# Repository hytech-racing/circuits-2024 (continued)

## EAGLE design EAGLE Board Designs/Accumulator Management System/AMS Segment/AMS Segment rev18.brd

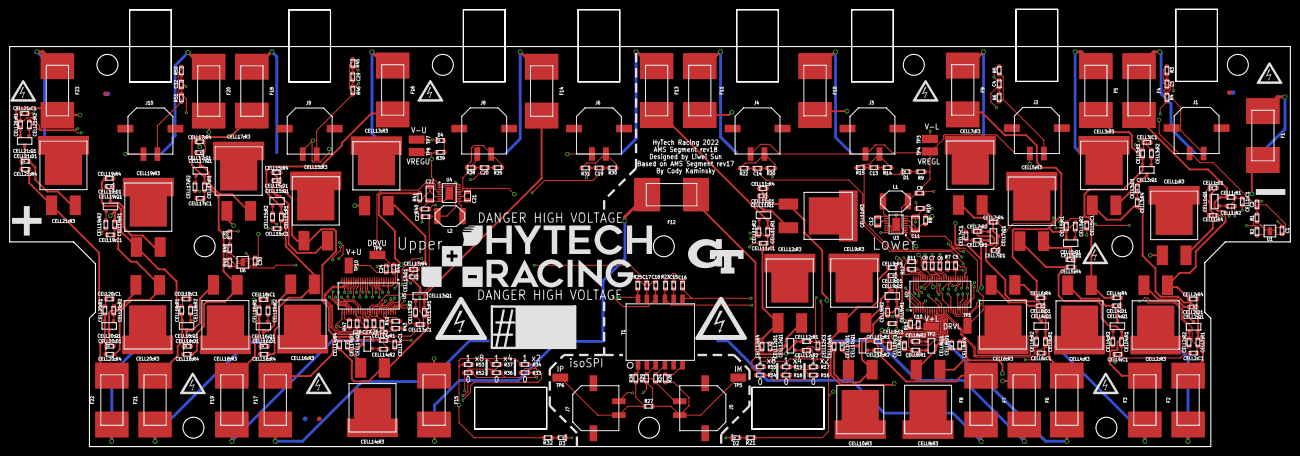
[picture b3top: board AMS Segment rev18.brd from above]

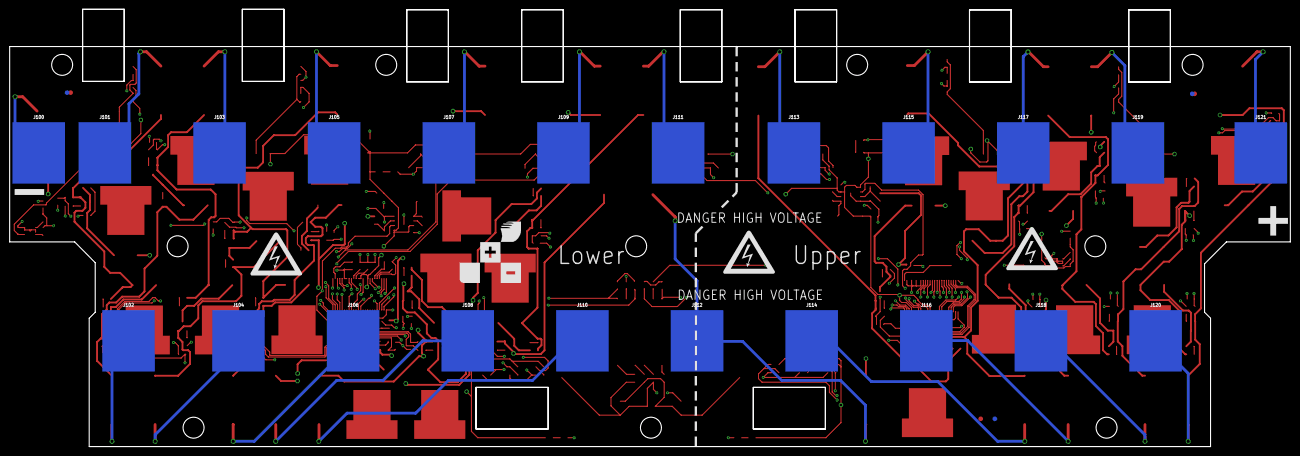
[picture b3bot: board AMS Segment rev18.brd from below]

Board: 4 copper layers, 275.2 x 94.0 mm, 347 parts (29 on the bottom side), 220 nets.

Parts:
C1, C30: CAPACITOR_0603_10V_0.1UF; 0603-CAP
C2, C31: CAPACITOR_0603_10V_3.3NF; 0603-CAP
C3, C4, C5, C13, C14, C19, C20, C28, C29, C32: CAPACITOR_0603_100V_10NF; 0603-CAP
C6, C7, C8, C23, C26, C27: CAPACITOR_0603_10V_1UF; 0603-CAP
C9, C25: CAPACITOR_0603_10V_22UF; 0603-CAP
C10, C24: CAPACITOR_0603_100V_0.1UF; 0603-CAP
C11, C22: CAPACITOR_1206_100V_2.2UF; 1206-CAP
C12, C21: CAPACITOR_0805_100V_0.22UF; 0805-CAP
C15, C17: CAPACITOR_0603_10V_10NF; 0603-CAP
C16, C18: CAPACITOR_0603_10V_15PF; 0603-CAP
CELL1:C1, CELL2:C1, CELL3:C1, CELL4:C1, CELL5:C1, CELL6:C1, CELL7:C1, CELL8:C1, CELL9:C1, CELL10:C1, CELL11:C1, CELL12:C1, CELL13:C1, CELL14:C1, CELL15:C1, CELL16:C1, CELL17:C1, CELL18:C1, CELL19:C1, CELL20:C1, CELL21:C1: CAPACITOR_0603_100V_10NF; 0603-CAP
CELL1:D1, CELL2:D1, CELL3:D1, CELL4:D1, CELL5:D1, CELL6:D1, CELL7:D1, CELL8:D1, CELL9:D1, CELL10:D1, CELL11:D1, CELL12:D1, CELL13:D1, CELL14:D1, CELL15:D1, CELL16:D1, CELL17:D1, CELL18:D1, CELL19:D1, CELL20:D1, CELL21:D1: LED_0603_RED; 0603-LED
CELL1:Q1, CELL2:Q1, CELL3:Q1, CELL4:Q1, CELL5:Q1, CELL6:Q1, CELL7:Q1, CELL8:Q1, CELL9:Q1, CELL10:Q1, CELL11:Q1, CELL12:Q1, CELL13:Q1, CELL14:Q1, CELL15:Q1, CELL16:Q1, CELL17:Q1, CELL18:Q1, CELL19:Q1, CELL20:Q1, CELL21:Q1: TRANSISTOR_P_MOS_SOT23_SI2369DS-T1-GE3; SOT-23
CELL1:R1, CELL2:R1, CELL3:R1, CELL4:R1, CELL5:R1, CELL6:R1, CELL7:R1, CELL8:R1, CELL9:R1, CELL10:R1, CELL11:R1, CELL12:R1, CELL13:R1, CELL14:R1, CELL15:R1, CELL16:R1, CELL17:R1, CELL18:R1, CELL19:R1, CELL20:R1, CELL21:R1: RESISTOR_0603_100; 0603-RES
CELL1:R2, CELL1:R4, CELL2:R2, CELL2:R4, CELL3:R2, CELL3:R4, CELL4:R2, CELL4:R4, CELL5:R2, CELL5:R4, CELL6:R2, CELL6:R4, CELL7:R2, CELL7:R4, CELL8:R2, CELL8:R4, CELL9:R2, CELL9:R4, CELL10:R2, CELL10:R4, CELL11:R2, CELL11:R4, CELL12:R2, CELL12:R4, CELL13:R2, CELL13:R4, CELL14:R2, CELL14:R4, CELL15:R2, CELL15:R4, CELL16:R2, CELL16:R4, CELL17:R2, CELL17:R4, CELL18:R2, CELL18:R4, CELL19:R2, CELL19:R4, CELL20:R2, CELL20:R4, CELL21:R2, CELL21:R4: RESISTOR_0603_1K; 0603-RES
CELL1:R3, CELL2:R3, CELL3:R3, CELL4:R3, CELL5:R3, CELL6:R3, CELL7:R3, CELL8:R3, CELL9:R3, CELL10:R3, CELL11:R3, CELL12:R3, CELL13:R3, CELL14:R3, CELL15:R3, CELL16:R3, CELL17:R3, CELL18:R3, CELL19:R3, CELL20:R3, CELL21:R3: RESISTOR_PWR263_7.5; PWR263
D1, D2, D3, D4: LED_0603_BLUE; 0603-LED
F1, F2, F3, F4, F5, F6, F7, F8, F9, F10, F11, F12, F13, F14, F15, F16, F17, F18, F19, F20, F21, F22, F23: FUSE_0885_1; 0885
J1, J2, J3, J4, J5, J6, J7, J8, J9, J10: CONNECTOR-2_MICROFIT_SMD_RIGHTANGLE_02_SINGLE_BLA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; MOLEX_MICROFIT_SMD_RIGHTANGLE_02_SINGLE
J100, J101, J102, J103, J104, J105, J106, J107, J108, J109, J110, J111, J112, J113, J114, J115, J116, J117, J118, J119, J120, J121: CONNECTOR-1_5222_; 5222
L1, L2: INDUCTOR_74451133_33UH; 74451133
R1, R4, R6, R7, R13, R15, R22, R31, R35, R44, R46, R47, R49, R51: RESISTOR_0603_100; 0603-RES
R2, R16, R17, R18, R19, R27, R33, R34, R36, R37, R48, R52, R53, R54, R55: RESISTOR_0603_DNP; 0603-RES
R3, R5, R14, R20, R30, R38, R45, R50: RESISTOR_0603_2.74K; 0603-RES
R8, R41: RESISTOR_0603_470; 0603-RES
R9, R11, R12, R21, R32, R39, R42, R43: RESISTOR_0603_1K; 0603-RES
R10, R40: RESISTOR_0603_374K; 0603-RES
R23, R25: RESISTOR_0603_402; 0603-RES
R24, R26, R28, R29: RESISTOR_0603_22; 0603-RES
T1: TRANSFORMER_HM2112ZNLT; HM2112ZNLT
TP1, TP2, TP3, TP4, TP5, TP6, TP7, TP8, TP9, TP10: TEST_POINT; MICRO_MINIATURE
U1, U6: SHT31-ARP-B; DFN-8
U2, U5: LTC6811-2; SSOP-48
U3, U4: LT3990-5; MSOP-16(MSE)
U$1, U$5, U$6, U$7, U$18, U$20, U$23, U$25: HV_0.50"
U$2, U$3, U$4, U$8, U$11, U$12, U$17, U$21, U$22, U$24: MOUNTING_M4
U$9, U$16: HV_1.00"
U$10: LOGO_GT_MEDIUM
U$13, U$14: DANGER_HIGH_VOLTAGE
U$15: NUMBER
U$19: LOGO_HYTECH_LARGE
U$26: LOGO_HYTECH_SQUARE_EXTRA_LARGE
U$27, U$28, U$29, U$31, U$32, U$33: FIDUCIAL_1MM
U$101, U$102, U$103: HV_LARGE

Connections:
C0L: C5.1, R7.2, U2.26
C0U: C28.1, R47.2, U5.26
C1L: CELL1:C1.1, CELL1:R1.2, U2.24
C1U: CELL13:C1.1, CELL13:R1.2, U5.24
C2L: CELL2:C1.1, CELL2:R1.2, U2.22
C2U: CELL14:C1.1, CELL14:R1.2, U5.22
C3L: CELL3:C1.1, CELL3:R1.2, U2.20
C3U: CELL15:C1.1, CELL15:R1.2, U5.20
C4L: CELL4:C1.1, CELL4:R1.2, U2.18
C4U: CELL16:C1.1, CELL16:R1.2, U5.18
C5L: CELL5:C1.1, CELL5:R1.2, U2.16
C5U: CELL17:C1.1, CELL17:R1.2, U5.16
C6L: CELL6:C1.1, CELL6:R1.2, U2.14
C6U: CELL18:C1.1, CELL18:R1.2, U5.14
C7L: CELL7:C1.1, CELL7:R1.2, U2.12
C7U: CELL19:C1.1, CELL19:R1.2, U5.12
C8L: CELL8:C1.1, CELL8:R1.2, U2.10
C8U: CELL20:C1.1, CELL20:R1.2, U5.10
C9L: CELL9:C1.1, CELL9:R1.2, U2.8
C9U: CELL21:C1.1, CELL21:R1.2, U5.2, U5.4, U5.6, U5.8
C10L: CELL10:C1.1, CELL10:R1.2, U2.6
C11L: CELL11:C1.1, CELL11:R1.2, U2.4
C12L: CELL12:C1.1, CELL12:R1.2, U2.2
CC0: F1.1, J100.1
CC1: F4.1, J101.1
CC2: F2.1, J102.1
CC3: F5.1, J103.1
CC4: F3.1, J104.1
CC5: F9.1, J105.1
CC6: F6.1, J106.1
CC7: F10.1, J107.1
CC8: F7.1, J108.1
CC9: F11.1, J109.1
CC10: F8.1, J110.1
CC11: F13.1, J111.1
CC12: F12.1, F15.1, J112.1
CC13: F14.1, J113.1
CC14: F17.1, J114.1
CC15: F16.1, J115.1
CC16: F19.1, J116.1
CC17: F18.1, J117.1
CC18: F21.1, J118.1
CC19: F20.1, J119.1
CC20: F22.1, J120.1
CC21: F23.1, J121.1
CELL1:LED: CELL1:D1.1, CELL1:R4.2
CELL1:QD: CELL1:D1.2, CELL1:Q1.3, CELL1:R3.2
CELL1:QG: CELL1:Q1.1, CELL1:R2.1
CELL2:LED: CELL2:D1.1, CELL2:R4.2
CELL2:QD: CELL2:D1.2, CELL2:Q1.3, CELL2:R3.2
CELL2:QG: CELL2:Q1.1, CELL2:R2.1
CELL3:LED: CELL3:D1.1, CELL3:R4.2
CELL3:QD: CELL3:D1.2, CELL3:Q1.3, CELL3:R3.2
CELL3:QG: CELL3:Q1.1, CELL3:R2.1
CELL4:LED: CELL4:D1.1, CELL4:R4.2
CELL4:QD: CELL4:D1.2, CELL4:Q1.3, CELL4:R3.2
CELL4:QG: CELL4:Q1.1, CELL4:R2.1
CELL5:LED: CELL5:D1.1, CELL5:R4.2
CELL5:QD: CELL5:D1.2, CELL5:Q1.3, CELL5:R3.2
CELL5:QG: CELL5:Q1.1, CELL5:R2.1
CELL6:LED: CELL6:D1.1, CELL6:R4.2
CELL6:QD: CELL6:D1.2, CELL6:Q1.3, CELL6:R3.2
CELL6:QG: CELL6:Q1.1, CELL6:R2.1
CELL7:LED: CELL7:D1.1, CELL7:R4.2
CELL7:QD: CELL7:D1.2, CELL7:Q1.3, CELL7:R3.2
CELL7:QG: CELL7:Q1.1, CELL7:R2.1
CELL8:LED: CELL8:D1.1, CELL8:R4.2
CELL8:QD: CELL8:D1.2, CELL8:Q1.3, CELL8:R3.2
CELL8:QG: CELL8:Q1.1, CELL8:R2.1
CELL9:LED: CELL9:D1.1, CELL9:R4.2
CELL9:QD: CELL9:D1.2, CELL9:Q1.3, CELL9:R3.2
CELL9:QG: CELL9:Q1.1, CELL9:R2.1
CELL10:LED: CELL10:D1.1, CELL10:R4.2
CELL10:QD: CELL10:D1.2, CELL10:Q1.3, CELL10:R3.2
CELL10:QG: CELL10:Q1.1, CELL10:R2.1
CELL11:LED: CELL11:D1.1, CELL11:R4.2
CELL11:QD: CELL11:D1.2, CELL11:Q1.3, CELL11:R3.2
CELL11:QG: CELL11:Q1.1, CELL11:R2.1
CELL12:LED: CELL12:D1.1, CELL12:R4.2
CELL12:QD: CELL12:D1.2, CELL12:Q1.3, CELL12:R3.2
CELL12:QG: CELL12:Q1.1, CELL12:R2.1
CELL13:LED: CELL13:D1.1, CELL13:R4.2
CELL13:QD: CELL13:D1.2, CELL13:Q1.3, CELL13:R3.2
CELL13:QG: CELL13:Q1.1, CELL13:R2.1
CELL14:LED: CELL14:D1.1, CELL14:R4.2
CELL14:QD: CELL14:D1.2, CELL14:Q1.3, CELL14:R3.2
CELL14:QG: CELL14:Q1.1, CELL14:R2.1
CELL15:LED: CELL15:D1.1, CELL15:R4.2
CELL15:QD: CELL15:D1.2, CELL15:Q1.3, CELL15:R3.2
CELL15:QG: CELL15:Q1.1, CELL15:R2.1
CELL16:LED: CELL16:D1.1, CELL16:R4.2
CELL16:QD: CELL16:D1.2, CELL16:Q1.3, CELL16:R3.2
CELL16:QG: CELL16:Q1.1, CELL16:R2.1
CELL17:LED: CELL17:D1.1, CELL17:R4.2
CELL17:QD: CELL17:D1.2, CELL17:Q1.3, CELL17:R3.2
CELL17:QG: CELL17:Q1.1, CELL17:R2.1
CELL18:LED: CELL18:D1.1, CELL18:R4.2
CELL18:QD: CELL18:D1.2, CELL18:Q1.3, CELL18:R3.2
CELL18:QG: CELL18:Q1.1, CELL18:R2.1
CELL19:LED: CELL19:D1.1, CELL19:R4.2
CELL19:QD: CELL19:D1.2, CELL19:Q1.3, CELL19:R3.2
CELL19:QG: CELL19:Q1.1, CELL19:R2.1
CELL20:LED: CELL20:D1.1, CELL20:R4.2
CELL20:QD: CELL20:D1.2, CELL20:Q1.3, CELL20:R3.2
CELL20:QG: CELL20:Q1.1, CELL20:R2.1
CELL21:LED: CELL21:D1.1, CELL21:R4.2
CELL21:QD: CELL21:D1.2, CELL21:Q1.3, CELL21:R3.2
CELL21:QG: CELL21:Q1.1, CELL21:R2.1
DRVL: TP1.1, U2.38, U3.4
DRVU: TP9.1, U4.4, U5.38
GPIO1L: C14.1, R22.2, U2.27
GPIO1U: C32.2, R51.1, U5.27
GPIO2L: C13.1, R15.2, U2.28
GPIO2U: C29.1, R46.2, U5.28
GPIO3L: C4.1, R6.2, U2.29
GPIO3U: C20.1, R35.2, U5.29
GPIO4L: C3.2, R4.2, U2.32
GPIO4U: C19.1, R31.2, U5.32
GPIO5L: C2.1, R1.1, R2.1, U2.33
GPIO5U: C31.1, R48.1, R49.2, U5.33
IM: J5.2, J7.2, R26.1, R27.1, R29.1, TP5.1
IML: C16.2, T1.7, U2.41
IMU: C18.2, T1.10, U5.41
IP: J5.1, J7.1, R24.1, R27.2, R28.1, TP6.1
IPL: R23.2, T1.9, U2.42
IPU: R25.2, T1.12, U5.42
unnamed: R40.2, U4.16
unnamed: D1.2, R9.1
unnamed: C21.2, L2.1, U4.9
unnamed: C21.1, U4.11
unnamed: D3.2, R32.1
unnamed: D2.2, R21.1
unnamed: R10.2, U3.16
unnamed: R54.1, R55.2, U2.48
unnamed: D4.2, R39.1
unnamed: C12.2, L1.1, U3.9
unnamed: C12.1, U3.11
unnamed: R48.2, U6.1
unnamed: R52.1, R53.2, U5.48
unnamed: C17.2, T1.11
unnamed: R29.2, T1.3
unnamed: R33.1, R34.2, U5.46
unnamed: R28.2, T1.1
unnamed: C15.2, T1.8
unnamed: R49.1, U6.4
unnamed: R26.2, T1.6
unnamed: R24.2, T1.4
unnamed: R36.1, R37.2, U5.47
unnamed: R42.2, R43.2, U5.43
unnamed: R16.1, R17.2, U2.46
unnamed: R18.1, R19.2, U2.47
unnamed: R42.1, U5.44
unnamed: J10.2, R50.1, R51.2
unnamed: R11.2, R12.1, U2.43
unnamed: R12.2, U2.44
unnamed: J9.2, R45.1, R46.1
unnamed: J8.2, R35.1, R38.1
unnamed: J6.2, R30.1, R31.1
unnamed: R1.2, U1.1
unnamed: R2.2, U1.4
unnamed: J4.2, R20.1, R22.1
unnamed: J3.2, R14.1, R15.1
unnamed: J2.2, R5.1, R6.1
unnamed: J1.2, R3.2, R4.1
unnamed: C18.1, R25.1
unnamed: C16.1, R23.1
S1L: CELL1:R2.2, U2.25
S1U: CELL13:R2.2, U5.25
S2L: CELL2:R2.2, U2.23
S2U: CELL14:R2.2, U5.23
S3L: CELL3:R2.2, U2.21
S3U: CELL15:R2.2, U5.21
S4L: CELL4:R2.2, U2.19
S4U: CELL16:R2.2, U5.19
S5L: CELL5:R2.2, U2.17
S5U: CELL17:R2.2, U5.17
S6L: CELL6:R2.2, U2.15
S6U: CELL18:R2.2, U5.15
S7L: CELL7:R2.2, U2.13
S7U: CELL19:R2.2, U5.13
S8L: CELL8:R2.2, U2.11
S8U: CELL20:R2.2, U5.11
S9L: CELL9:R2.2, U2.9
S9U: CELL21:R2.2, U5.9
S10L: CELL10:R2.2, U2.7
S11L: CELL11:R2.2, U2.5
S12L: CELL12:R2.2, U2.3
SENSE1: CELL1:Q1.2, CELL1:R1.1, CELL2:R3.1, CELL2:R4.1, F4.2
SENSE2: CELL2:Q1.2, CELL2:R1.1, CELL3:R3.1, CELL3:R4.1, F2.2
SENSE3: CELL3:Q1.2, CELL3:R1.1, CELL4:R3.1, CELL4:R4.1, F5.2
SENSE4: CELL4:Q1.2, CELL4:R1.1, CELL5:R3.1, CELL5:R4.1, F3.2
SENSE5: CELL5:Q1.2, CELL5:R1.1, CELL6:R3.1, CELL6:R4.1, F9.2
SENSE6: CELL6:Q1.2, CELL6:R1.1, CELL7:R3.1, CELL7:R4.1, F6.2
SENSE7: CELL7:Q1.2, CELL7:R1.1, CELL8:R3.1, CELL8:R4.1, F10.2
SENSE8: CELL8:Q1.2, CELL8:R1.1, CELL9:R3.1, CELL9:R4.1, F7.2
SENSE9: CELL9:Q1.2, CELL9:R1.1, CELL10:R3.1, CELL10:R4.1, F11.2
SENSE10: CELL10:Q1.2, CELL10:R1.1, CELL11:R3.1, CELL11:R4.1, F8.2
SENSE11: CELL11:Q1.2, CELL11:R1.1, CELL12:R3.1, CELL12:R4.1, F13.2
SENSE12: CELL12:Q1.2, CELL12:R1.1, F12.2, R8.1, R13.2
SENSE13: CELL13:Q1.2, CELL13:R1.1, CELL14:R3.1, CELL14:R4.1, F14.2
SENSE14: CELL14:Q1.2, CELL14:R1.1, CELL15:R3.1, CELL15:R4.1, F17.2
SENSE15: CELL15:Q1.2, CELL15:R1.1, CELL16:R3.1, CELL16:R4.1, F16.2
SENSE16: CELL16:Q1.2, CELL16:R1.1, CELL17:R3.1, CELL17:R4.1, F19.2
SENSE17: CELL17:Q1.2, CELL17:R1.1, CELL18:R3.1, CELL18:R4.1, F18.2
SENSE18: CELL18:Q1.2, CELL18:R1.1, CELL19:R3.1, CELL19:R4.1, F21.2
SENSE19: CELL19:Q1.2, CELL19:R1.1, CELL20:R3.1, CELL20:R4.1, F20.2
SENSE20: CELL20:Q1.2, CELL20:R1.1, CELL21:R3.1, CELL21:R4.1, F22.2
SENSE21: CELL21:Q1.2, CELL21:R1.1, F23.2, R41.1, R44.1
V+L: C10.1, R13.1, TP2.1, U2.1
V+U: C24.1, R44.2, TP10.1, U5.1
V-L: C1.1, C2.2, C3.1, C4.2, C5.2, C6.2, C7.2, C8.2, C9.2, C10.2, C11.2, C13.2, C14.2, C15.1, CELL1:C1.2, CELL1:R3.1, CELL1:R4.1, CELL2:C1.2, CELL3:C1.2, CELL4:C1.2, CELL5:C1.2, CELL6:C1.2, CELL7:C1.2, CELL8:C1.2, CELL9:C1.2, CELL10:C1.2, CELL11:C1.2, CELL12:C1.2, D1.1, D2.1, F1.2, R3.1, R5.2, R7.1, R10.1, R11.1, R14.2, R16.2, R18.2, R20.2, R54.2, TP3.1, U1.2, U1.3, U1.7, U1.8, U1.PAD, U2.30, U2.31, U2.45, U3.8, U3.17
V-U: C17.1, C19.2, C20.2, C22.2, C23.2, C24.2, C25.2, C26.2, C27.2, C28.2, C29.2, C30.2, C31.2, C32.1, CELL13:C1.2, CELL13:R3.1, CELL13:R4.1, CELL14:C1.2, CELL15:C1.2, CELL16:C1.2, CELL17:C1.2, CELL18:C1.2, CELL19:C1.2, CELL20:C1.2, CELL21:C1.2, D3.1, D4.1, F15.2, R30.2, R33.2, R36.2, R38.2, R40.1, R43.1, R45.2, R47.1, R50.2, R52.2, TP7.1, U4.8, U4.17, U5.30, U5.31, U6.2, U6.3, U6.7, U6.8, U6.PAD
VINL: C11.1, R8.2, U3.6
VINU: C22.1, R41.2, U4.6
VREF1L: C7.1, U2.35
VREF1U: C26.1, U5.35
VREF2L: C6.1, U2.34
VREF2U: C27.1, U5.34
VREGL: C1.2, C8.1, C9.1, J1.1, J2.1, J3.1, J4.1, L1.2, R9.2, R17.1, R19.1, R21.2, R55.1, TP4.1, U1.5, U2.36, U2.37, U2.40, U3.1, U3.2, U3.13
VREGU: C23.1, C25.1, C30.1, J6.1, J8.1, J9.1, J10.1, L2.2, R32.2, R34.1, R37.1, R39.2, R53.1, TP8.1, U4.1, U4.2, U4.13, U5.36, U5.37, U5.40, U5.45, U6.5

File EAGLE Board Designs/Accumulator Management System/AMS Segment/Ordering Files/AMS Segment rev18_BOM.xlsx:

Board Quantity | Value | Reference Designator | CAPACITANCE | COLOR | CURRENT | CURRENT_RATED | CURRENT_SATURATION | DCR | DKPN | GAUGE | INDUCTANCE | MANUFACTURER | MODEL | Mouser Part Number | MPN | Alternative MPN | POWER | RESISTANCE | TOLERANCE | TOLERANCE_B | TOLERANCE_RESISTANCE | VOLTAGE | VOLTAGE_CONTINUOUS | VOLTAGE_MAX
2 | CAPACITOR_0603_100V_0.1UF | C10, C24 | 0.1µF |  |  |  |  |  | 311-1523-1-ND |  |  | Yageo |  | 603-CC603KRX7R0BB104 | CC0603KRX7R0BB104 |  |  |  | 0.1 |  |  | 100V
31 | CAPACITOR_0603_100V_10NF | C3, C4, C5, C13, C14, C19, C20, C28, C29, C32, CELL1:C1, CELL2:C1, CELL3:C1, CE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 | 10nF |  |  |  |  |  | 311-1788-1-ND |  |  | Yageo |  | 603-CC603KRX7R0BB103 | CC0603KRX7R0BB103 |  |  |  | 0.1 |  |  | 100V
2 | CAPACITOR_0603_10V_0.1UF | C1, C30 | 0.1µF |  |  |  |  |  | 720-1688-1-ND |  |  | Vishay Vitramon |  | 77-VJ0603Y104JXQPBC | VJ0603Y104JXQPW1BC |  |  |  | 0.05 |  |  | 10V
2 | CAPACITOR_0603_10V_10NF | C15, C17 | 10nF |  |  |  |  |  | 311-4054-1-ND |  |  | Yageo |  | 603-CC603KRX7R6BB103 | CC0603KRX7R6BB103 |  |  |  | 0.1 |  |  | 10V
2 | CAPACITOR_0603_10V_15PF | C16, C18 | 15pF |  |  |  |  |  | 720-VJ0603A150FXQPW1BCCT-ND |  |  | Vishay Vitramon |  | 77-VJ0603A150FXQPBC | VJ0603A150FXQPW1BC |  |  |  | 0.01 |  |  | 10V
6 | CAPACITOR_0603_10V_1UF | C6, C7, C8, C23, C26, C27 | 1µF |  |  |  |  |  | 311-1796-1-ND |  |  | Yageo |  | 603-CC603KRX7R6BB105 | CC0603KRX7R6BB105 |  |  |  | 0.1 |  |  | 10V
2 | CAPACITOR_0603_10V_22UF | C9, C25 | 22µF |  |  |  |  |  | 490-10476-1-ND |  |  | Murata Electronics |  | 81-GRM188R61A226ME5D | GRM188R61A226ME15D |  |  |  | 0.2 |  |  | 10V
2 | CAPACITOR_0603_10V_3.3NF | C2, C31 | 3.3nF |  |  |  |  |  | 732-7759-1-ND |  |  | WÃ¼rth Elektronik |  | 710-885012006016 | 885012006016 |  |  |  | 0.05 |  |  | 10V
2 | CAPACITOR_0805_100V_0.22UF | C12, C21 | 0.22µF |  |  |  |  |  | 399-8049-1-ND |  |  | KEMET |  | 80-C0805C224K1R | C0805C224K1RACTU |  |  |  | 0.1 |  |  | 100V
2 | CAPACITOR_1206_100V_2.2UF | C11, C22 | 2.2µF |  |  |  |  |  | 478-12144-1-ND |  |  | AVX Corporation |  | 581-12061C225K4T2A | 12061C225K4T2A |  |  |  | 0.1 |  |  | 100V
22 | CONNECTOR-1_5222_ | J100, J101, J102, J103, J104, J105, J106, J107, J108, J109, J110, J111, J112, J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 |  |  |  |  |  |  | 36-5222-ND |  |  | Keystone Electronics | SPRING | 534-5222 | 5222
10 | CONNECTOR-2_MICROFIT_SMD_RIGHTANGLE_02_SINGLE_BLACK | J1, J2, J3, J4, J5, J6, J7, J8, J9, J10 |  |  |  |  |  |  | WM14310CT-ND |  |  | Molex |  | 538-43650-0214 | 436500214
20 | CRIMP_MICROFIT_20-24 | O17, O18, O19, O20, O21, O22, O23, O24, O25, O26, O27, O28, O29, O30, O31, O32,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 |  |  |  |  |  |  | WM2776CT-ND | 20-24 |  | Molex |  | 538-43030-0003 | 430300003
23 | FUSE_0885_1 | F1, F2, F3, F4, F5, F6, F7, F8, F9, F10, F11, F12, F13, F14, F15, F16, F17, F18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 |  |  | 1A |  |  |  | F10985CT-ND |  |  | Littelfuse Inc. |  | 576-0885001.DR | 0885001.DR |  |  |  |  |  |  | 500V
2 | INDUCTOR_74451133_33UH | L1, L2 |  |  |  | 0.6A | 0.15A | 0.19Ohms | 732-1410-1-ND |  | 33µH | WÃ¼rth Elektronik |  | 710-74451133 | 74451133 |  |  |  | 0.2
4 | LED_0603_BLUE | D1, D2, D3, D4 |  | Blue |  |  |  |  | 754-1789-1-ND |  |  | Kingbright |  | 604-APT1608VBC/D | APT1608VBC/D
21 | LED_0603_RED | CELL1:D1, CELL2:D1, CELL3:D1, CELL4:D1, CELL5:D1, CELL6:D1, CELL7:D1, CELL8:D1,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 |  | Red |  |  |  |  | 754-1786-1-ND |  |  | Kingbright |  | 604-APT1608SECKJ3PRV | APT1608SECK/J3-PRV
2 | LT3990-5 | U3, U4 |  |  |  |  |  |  | LT3990EMSE-5#PBF-ND |  |  | Analog Devices Inc. |  | 584-LT3990EMSE-5#PBF | LT3990EMSE-5#PBF | LT3990HMSE-5#PBF
2 | LTC6811-2 | U2, U5 |  |  |  |  |  |  | LTC6811IG-2#3ZZPBF-ND |  |  | Analog Devices Inc. |  | 584-6811IG-2#3ZZPB | LTC6811IG-2#3ZZPBF
10 | PLUG-2_MICROFIT_HORIZONTAL | O9, O10, O11, O12, O13, O14, O15, O16, O33, O34 |  |  |  |  |  |  | WM1845-ND |  |  | Molex |  | Molex | 436450200
35 | RESISTOR_0603_100 | CELL1:R1, CELL2:R1, CELL3:R1, CELL4:R1, CELL5:R1, CELL6:R1, CELL7:R1, CELL8:R1,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 |  |  |  |  |  |  | 311-100HRCT-ND |  |  | Yageo |  | 603-RC0603FR-07100RL | RC0603FR-07100RL |  | 0.1W | 100 | 0.01 |  |  |  | 3.16V | 75V
50 | RESISTOR_0603_1K | CELL1:R2, CELL1:R4, CELL2:R2, CELL2:R4, CELL3:R2, CELL3:R4, CELL4:R2, CELL4:R4,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 |  |  |  |  |  |  | 311-1.00KHRCT-ND |  |  | Yageo |  | 603-RC0603FR-071KL | RC0603FR-071KL |  | 0.1W | 1k | 0.01 |  |  |  | 10.00V | 75V
8 | RESISTOR_0603_2.74K | R3, R5, R14, R20, R30, R38, R45, R50 |  |  |  |  |  |  | P20020CT-ND |  |  | Panasonic Electronic Components |  | 667-ERJ-PB3B2741V | ERJ-PB3B2741V |  | 0.2W | 2.74k | 1E-3 |  |  |  | 23.41V | 150V
4 | RESISTOR_0603_22 | R24, R26, R28, R29 |  |  |  |  |  |  | 311-22.0HRCT-ND |  |  | Yageo |  | 603-RC0603FR-0722RL | RC0603FR-0722RL |  | 0.1W | 22 | 0.01 |  |  |  | 1.48V | 75V
2 | RESISTOR_0603_374K | R10, R40 |  |  |  |  |  |  | 311-374KHRCT-ND |  |  | Yageo |  | 603-RC0603FR-07374KL | RC0603FR-07374KL |  | 0.1W | 374k | 0.01 |  |  |  | 75V | 75V
2 | RESISTOR_0603_402 | R23, R25 |  |  |  |  |  |  | 311-402HRCT-ND |  |  | Yageo |  | 603-RC0603FR-07402RL | RC0603FR-07402RL |  | 0.1W | 402 | 0.01 |  |  |  | 6.34V | 75V
2 | RESISTOR_0603_470 | R8, R41 |  |  |  |  |  |  | P470BYCT-ND |  |  | Panasonic Electronic Components |  | 667-ERJ-PA3F4700V | ERJ-PA3F4700V |  | 0.25W | 470 | 0.01 |  |  |  | 10.84V | 150V
21 | RESISTOR_PWR263_7.5 | CELL1:R3, CELL2:R3, CELL3:R3, CELL4:R3, CELL5:R3, CELL6:R3, CELL7:R3, CELL8:R3,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 |  |  |  |  |  |  | PWR263S-35-7R50J-ND |  |  | Bourns Inc. |  | 652-PWR263S357R50J | PWR263S-35-7R50J |  | 3.5W | 7.5 | 0.05 |  |  |  | 5.123V | 5.123V
2 | SHT31-ARP-B | U1, U6 |  |  |  |  |  |  | 1649-1012-1-ND |  |  | Sensirion AG |  | 403-SHT31-ARP-B | SHT31-ARP-B
10 | TEST_POINT | TP1, TP2, TP3, TP4, TP5, TP6, TP7, TP8, TP9, TP10 |  |  |  |  |  |  | 36-5015CT-ND |  |  | Keystone Electronics |  | 534-5015 | 5015
8 | THERMISTOR | O1, O2, O3, O4, O5, O6, O7, O8 |  |  |  |  |  |  | 56-NTCALUG02A103F161A-ND |  |  | Vishay Beyschlag/Draloric/BC Components |  | 594-NTLUG02A103F161A | NTCALUG02A103F161A |  |  |  |  | 5.0000000000000001E-3 | 0.01
1 | TRANSFORMER_HM2112ZNLT | T1 |  |  |  |  |  |  | 1840-1036-1-ND |  |  | Pulse Electronics |  | 673-HM2112ZNLT | HM2112ZNLT
21 | TRANSISTOR_P_MOS_SOT23_SI2369DS-T1-GE3 | CELL1:Q1, CELL2:Q1, CELL3:Q1, CELL4:Q1, CELL5:Q1, CELL6:Q1, CELL7:Q1, CELL8:Q1,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 |  |  |  |  |  |  | SI2369DS-T1-GE3CT-ND |  |  | Vishay Siliconix |  | 78-SI2369DS-T1-GE3 | SI2369DS-T1-GE3 | SI2369DS-T1-BE3
15 | RESISTOR_0603_DNP | R2, R16, R17, R18, R19, R27, R33, R34, R36, R37, R48, R52, R53, R54, R55 |  |  |  |  |  |  |  |  |  |  |  |  |  |  |  | DNP

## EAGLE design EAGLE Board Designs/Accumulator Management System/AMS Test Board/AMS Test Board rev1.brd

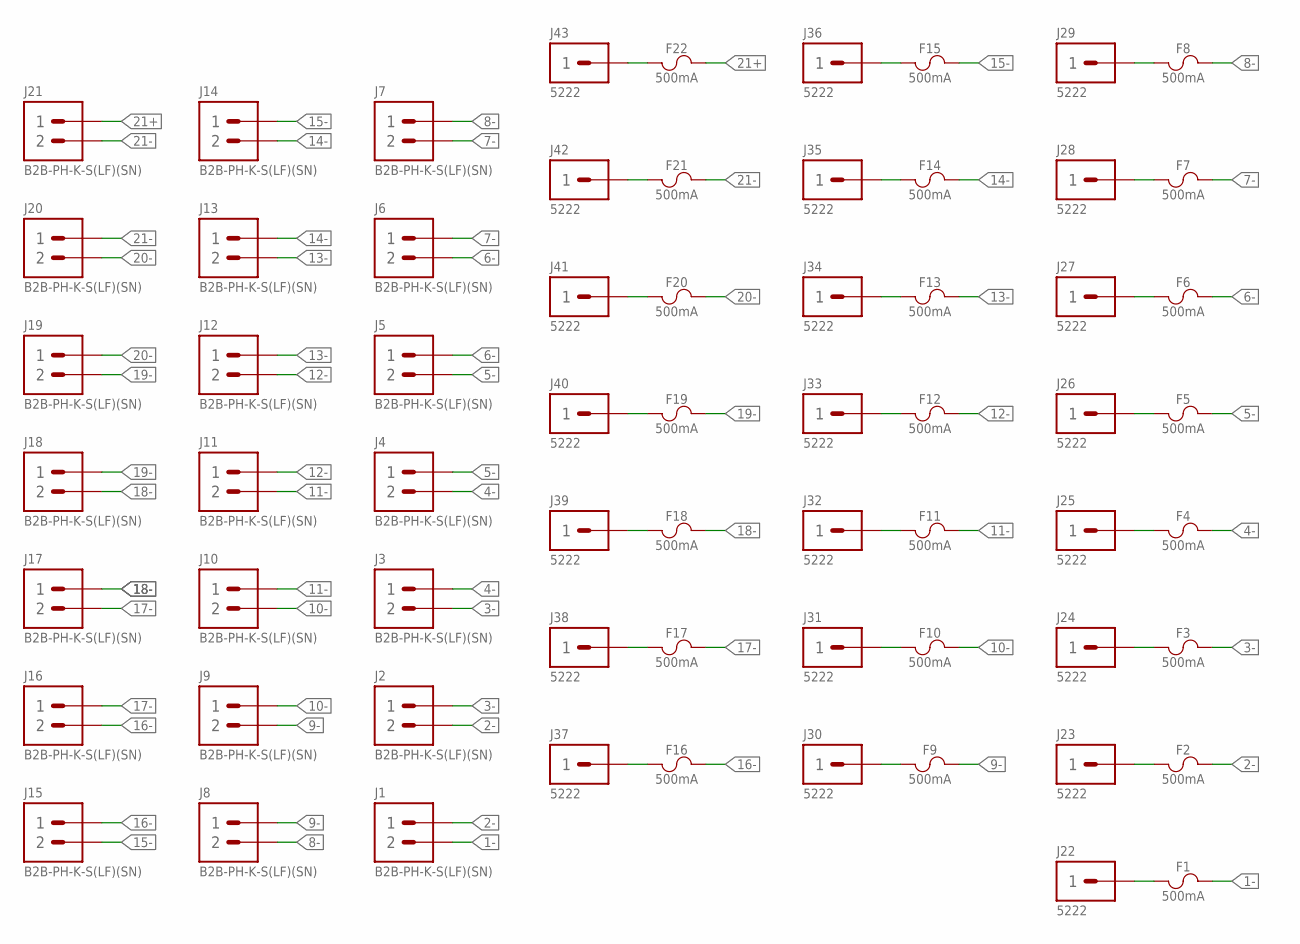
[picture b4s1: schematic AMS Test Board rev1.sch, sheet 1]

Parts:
F1, F2, F3, F4, F5, F6, F7, F8, F9, F10, F11, F12, F13, F14, F15, F16, F17, F18, F19, F20, F21, F22: FUSE_OMF_125_.5A; OMF_125
J1, J2, J3, J4, J5, J6, J7, J8, J9, J10, J11, J12, J13, J14, J15, J16, J17, J18, J19, J20, J21: CONNECTOR-2__B2B-PH-K; B2B-PH-K
J22, J23, J24, J25, J26, J27, J28, J29, J30, J31, J32, J33, J34, J35, J36, J37, J38, J39, J40, J41, J42, J43: CONNECTOR-1_5222; 5222

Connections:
1-: F1.2, J1.2
2-: F2.2, J1.1, J2.2
3-: F3.2, J2.1, J3.2
4-: F4.2, J3.1, J4.2
5-: F5.2, J4.1, J5.2
6-: F6.2, J5.1, J6.2
7-: F7.2, J6.1, J7.2
8-: F8.2, J7.1, J8.2
9-: F9.2, J8.1, J9.2
10-: F10.2, J9.1, J10.2
11-: F11.2, J10.1, J11.2
12-: F12.2, J11.1, J12.2
13-: F13.2, J12.1, J13.2
14-: F14.2, J13.1, J14.2
15-: F15.2, J14.1, J15.2
16-: F16.2, J15.1, J16.2
17-: F17.2, J16.1, J17.2
18-: F18.2, J17.1, J18.2
19-: F19.2, J18.1, J19.2
20-: F20.2, J19.1, J20.2
21+: F22.2, J21.1
21-: F21.2, J20.1, J21.2
unnamed: F1.1, J22.1
unnamed: F2.1, J23.1
unnamed: F3.1, J24.1
unnamed: F4.1, J25.1
unnamed: F5.1, J26.1
unnamed: F6.1, J27.1
unnamed: F7.1, J28.1
unnamed: F8.1, J29.1
unnamed: F9.1, J30.1
unnamed: F10.1, J31.1
unnamed: F11.1, J32.1
unnamed: F12.1, J33.1
unnamed: F13.1, J34.1
unnamed: F14.1, J35.1
unnamed: F15.1, J36.1
unnamed: F16.1, J37.1
unnamed: F17.1, J38.1
unnamed: F18.1, J39.1
unnamed: F19.1, J40.1
unnamed: F20.1, J41.1
unnamed: F21.1, J42.1
unnamed: F22.1, J43.1

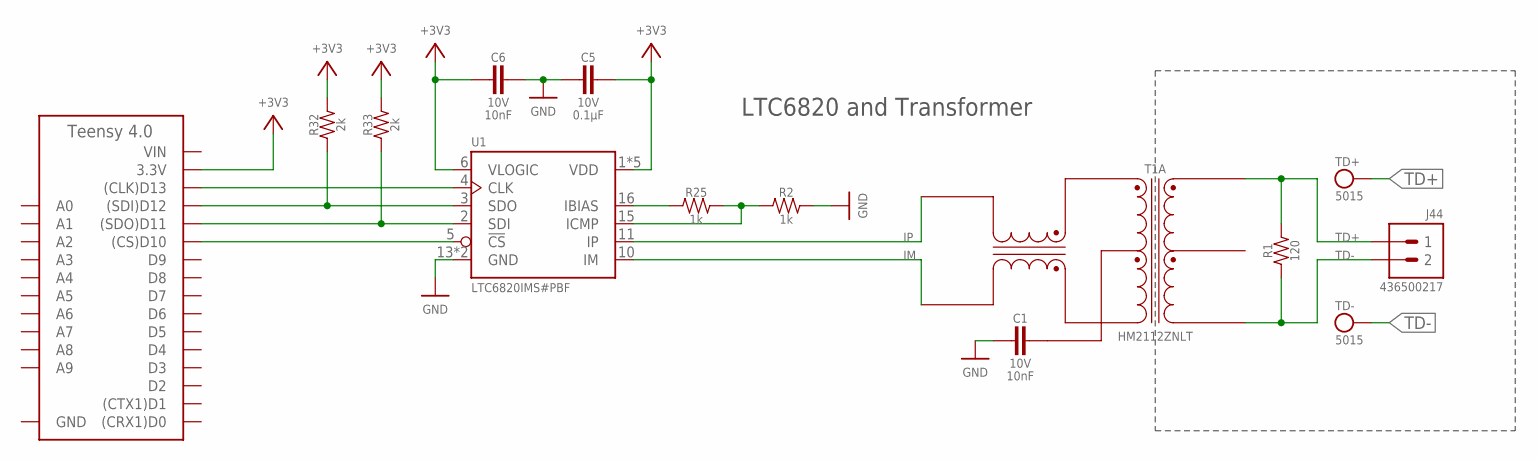
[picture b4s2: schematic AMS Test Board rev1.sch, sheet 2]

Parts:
A1: TEENSY_4.0; TEENSY_SHORT
C1, C6: CAPACITOR_0603_10V_10NF; 0603-CAP
C5: CAPACITOR_0603_10V_0.1UF; 0603-CAP
J44: CONNECTOR-2_MF_T_V_; MOLEX_MICROFIT_PTH_VERTICAL_02_SINGLE
R1: RESISTOR_0603_120; 0603-RES
R2, R25: RESISTOR_0603_1K; 0603-RES
R32, R33: RESISTOR_0603_2K; 0603-RES
T1: TRANSFORMER_HM2112ZNLT_AIRGAP; HM2112ZNLT_AIRGAP
TD+: TEST_POINT; MICRO_MINIATURE
TD-: TEST_POINT; MICRO_MINIATURE
U1: LTC6820; MSOP-16

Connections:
+3V3: A1.3.3V, C5.1, C6.2, R32.2, R33.2, U1.1 (VDD), U1.6 (VLOGIC), U1.7 (VDD), U1.8 (VDD), U1.9 (VDD), U1.12 (VDD)
GND: A1.AGND/GND (GND), A1.GND, C1.2, C5.2, C6.1, R2.2
IM: T1.10 (TD-), U1.10 (IM)
IP: T1.12 (TD+), U1.11 (IP)
unnamed: C1.1, T1.11 (TCT)
unnamed: A1.D13 ((CLK)D13), U1.4 (CLK)
unnamed: A1.D12 ((SDI)D12), R32.1, U1.3 (SDO)
unnamed: A1.D11 ((SDO)D11), R33.1, U1.2 (SDI)
unnamed: A1.D10 ((CS)D10), U1.5 (!CS)
unnamed: U1.13 (GND), U1.14 (GND)
unnamed: R25.1, U1.16 (IBIAS)
unnamed: R2.1, R25.2, U1.15 (ICMP)
TD+: J44.1, R1.2, T1.1 (MX+), TD+.1
TD-: J44.2, R1.1, T1.3 (MX-), TD-.1
VIN: A1.VIN

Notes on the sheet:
LTC6820 and Transformer

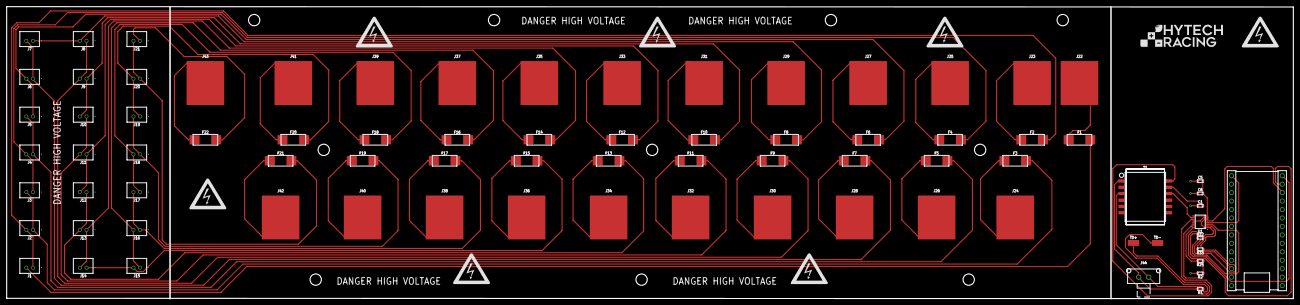
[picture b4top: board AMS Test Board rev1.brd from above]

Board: 2 copper layers, 386.6 x 87.7 mm, 104 parts (1 on the bottom side), 58 nets.

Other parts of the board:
U$1, U$2, U$3, U$4, U$20, U$21, U$22, U$29, U$30, U$31: MOUNTING_M3
U$5, U$6, U$7, U$8, U$9, U$10, U$11, U$12: HV_LARGE
U$13, U$14, U$15, U$16, U$17, U$18: DANGER_HIGH_VOLTAGE
U$19: LOGO_HYTECH_MEDIUM
